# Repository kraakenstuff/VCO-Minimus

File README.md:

# VCO-Minimus
3U Eurorack 3340 based VCO

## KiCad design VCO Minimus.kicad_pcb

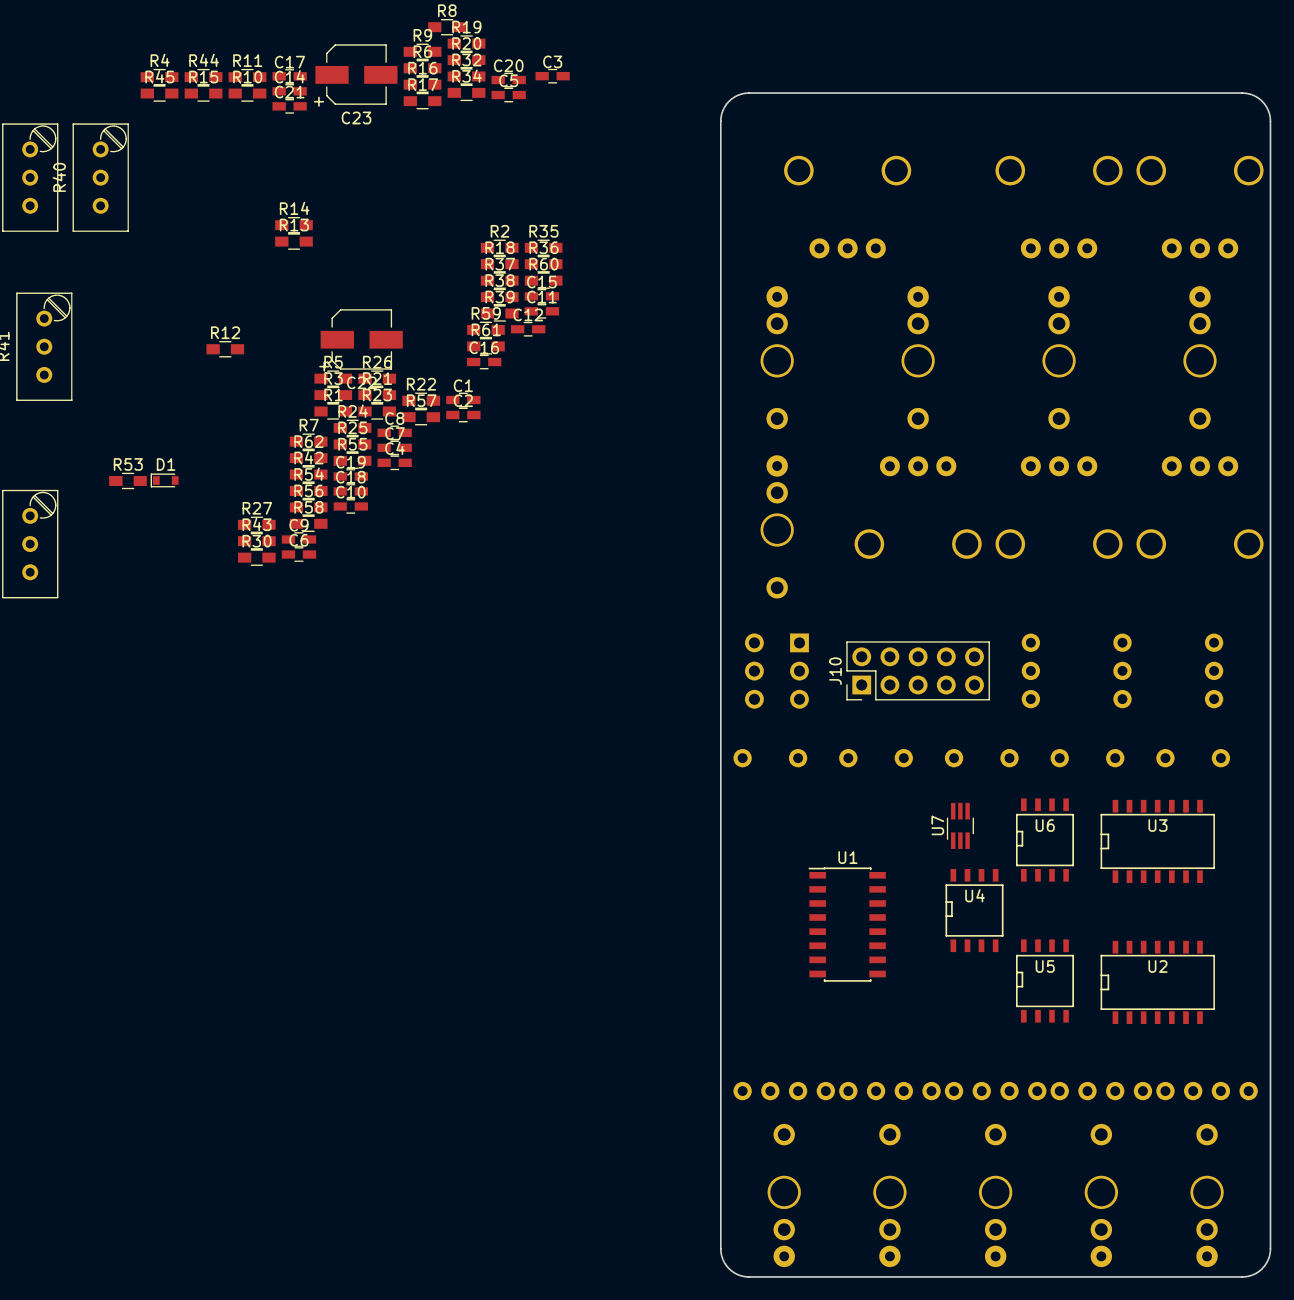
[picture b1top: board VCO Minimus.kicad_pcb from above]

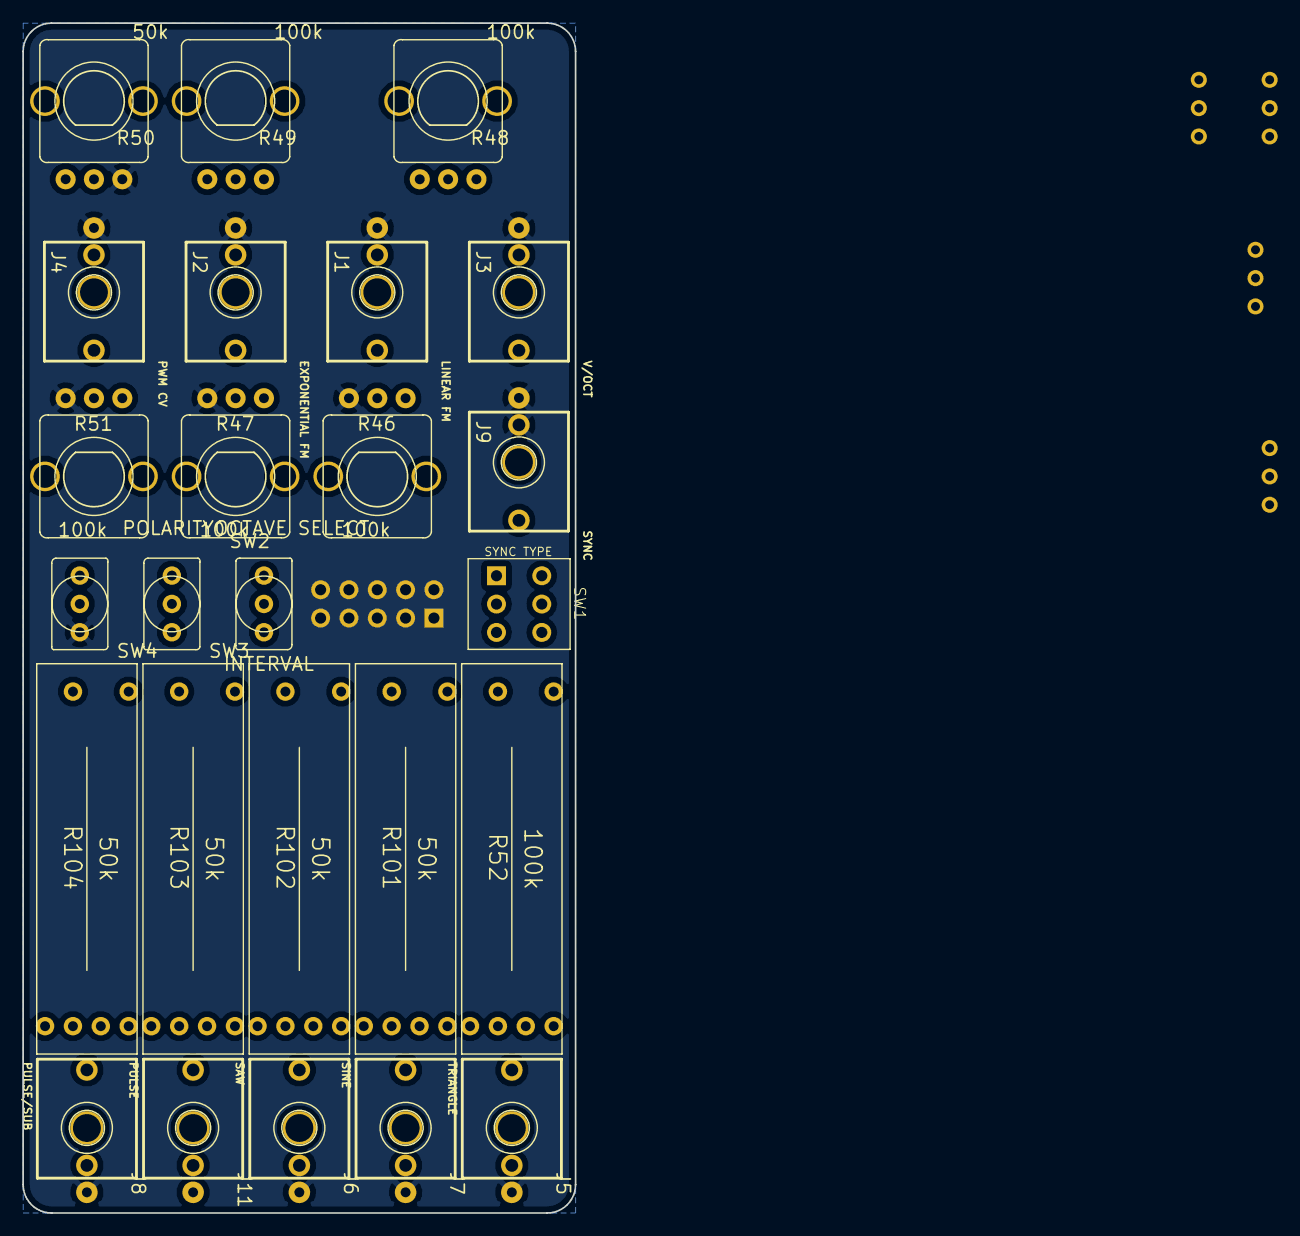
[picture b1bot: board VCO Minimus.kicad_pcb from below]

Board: 2 copper layers, 49.5 x 106.7 mm, 109 parts (25 on the bottom side), 74 nets, no tracks yet.

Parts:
C1: 22p; C_0603_HandSoldering
C2: 33p; C_0603_HandSoldering
C3: 47p; C_0603_HandSoldering
C4, C5, C6: 1n; C_0603_HandSoldering
C7, C8: 10n; C_0603_HandSoldering
C9, C10, C11, C12, C14, C15, C16, C17, C18, C19, C20: 100n; C_0603_HandSoldering
C21: 220n; C_0603_HandSoldering
C22, C23: 10u; CP_Elec_5x5.3
D1: 1N4148; D_0603
J1: LINEAR FM; PJ301M-12
J2: EXPONENTIAL FM; PJ301M-12
J3: V/OCT; PJ301M-12
J4: PWM CV; PJ301M-12
J5: TRIANGLE; PJ301M-12
J6: SAW; PJ301M-12
J7: SINE; PJ301M-12
J8: PULSE/SUB; PJ301M-12
J9: SYNC; PJ301M-12
J10: POWER; Pin_Header_Straight_2x05_Pitch2.54mm
J11: PULSE; PJ301M-12
R1: 390; R_0603_HandSoldering
R2, R3: 470; R_0603_HandSoldering
R4: 820; R_0603_HandSoldering
R5, R6: 1.5k; R_0603_HandSoldering
R7, R8: 1.8k; R_0603_HandSoldering
R9, R10: 2k; R_0603_HandSoldering
R11, R12: 2.2k; R_0603_HandSoldering
R13, R14, R15: 3k; R_0603_HandSoldering
R16, R17: 5.6k; R_0603_HandSoldering
R18, R19, R20, R21, R22, R23, R24, R25, R26, R27: 10k; R_0603_HandSoldering
R28, R29: 10k; Potentiometer_Trimmer_Bourns_3296W
R30: 15k; R_0603_HandSoldering
R32, R34: 20k; R_0603_HandSoldering
R35: 22k; R_0603_HandSoldering
R36: 24k; R_0603_HandSoldering
R37: 30k; R_0603_HandSoldering
R38, R39: 47k; R_0603_HandSoldering
R40, R41: 50k; Potentiometer_Trimmer_Bourns_3296W
R42, R43, R44, R45: 100k; R_0603_HandSoldering
R46, R47, R48, R49, R51: 100k; POT-9MM-ALPHA
R50: 50k; POT-9MM-ALPHA
R52: 100k; POT-SLIDER-LED-ALPHA-RA2045F-20
R53: 120k; R_0603_HandSoldering
R54: 300k; R_0603_HandSoldering
R55: 360k; R_0603_HandSoldering
R56, R57, R58, R59: 1M; R_0603_HandSoldering
R60: 1.5M; R_0603_HandSoldering
R61: 3.3M; R_0603_HandSoldering
R62: 10M; R_0603_HandSoldering
R101, R102, R103, R104: 50k; POT-SLIDER-LED-ALPHA-RA2045F-20
SW1: SYNC TYPE; DPDT_Toggle_108-2MD1T2B3M1QE-EVX
SW2: INTERVAL; SPDT-SUB
SW3: OCTAVE SELECT; SPDT-SUB
SW4: POLARITY; SPDT-SUB
U1: CEM3340; SOIC-16_3.9x9.9mm_Pitch1.27mm
U2: CD4070; SOIC-14_N
U3: CD4013; SOIC-14_N
U4, U5: TL072; SOIC-8-N
U6: TL071; SOIC-8-N
U7: DMMT3904W; SOT-363_SC-70-6_Handsoldering

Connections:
+12V: C11.2, C12.1, C18.1, C19.1, C20.1, C23.1, J10.9, J10.10, R22.2, R23.2, R26.2, R34.1, R37.1, R48.1, R49.1, R50.1, R55.2, R60.1, R62.2, SW4.3, U2.14, U3.14, U4.8, U5.8, U6.7
-12V: C15.2, C16.2, C17.2, C22.2, J10.1, J10.2, R4.1, R41.2, R48.3, R49.3, U4.4, U5.4, U6.4
GND: C2.1, C3.1, C4.2, C6.1, C7.1, C8.1, C9.2, C10.1, C11.1, C12.2, C14.1, C15.1, C16.1, C17.1, C18.2, C19.2, C20.2, C22.1, C23.2, J1.1, J2.1, J3.1, J4.1, J5.1, J6.1, J7.1, J8.1, J9.1, J9.2, J10.3, J10.4, J10.5, J10.6, J10.7, J10.8, R7.2, R8.2, R10.2, R11.1, R12.1, R13.1, R14.2, R19.1, R20.1, R21.1, R29.1, R46.3, R47.3, R50.3, R51.3, SW4.1, U1.12, U2.2, U2.7, U2.9, U3.4, U3.6, U3.7, U3.8, U3.10, U6.3
unnamed: C1.1, R26.1, R27.1, U5.6
unnamed: C1.2, R15.1, R27.2, U5.7
unnamed: C2.2, R24.2, U5.3
unnamed: C3.2, R35.2, R59.1, U2.1
unnamed: C4.1, U1.11
unnamed: C5.1, J9.3
unnamed: C5.2, SW1.5
unnamed: C6.2, R18.2, R58.1, U1.5
unnamed: C7.2, R3.1
unnamed: C8.2, R2.1
unnamed: C9.1, U1.16
unnamed: C10.2, R4.2, R16.1, R28.2, U1.3
unnamed: C14.2, SW1.3
unnamed: C21.1, R46.1
unnamed: C21.2, J1.3
unnamed: D1.1, R17.1, R20.2
unnamed: D1.2, U1.6
unnamed: J2.3, R47.1
unnamed: J3.3, R43.2
unnamed: J4.3, R51.1
unnamed: J5.3, R5.2, R13.2
unnamed: J6.3, R6.2, R14.1
unnamed: J7.3, R9.2, R10.1
unnamed: J8.3, R8.1, R15.2
unnamed: R1.1, R41.1, U7.4
unnamed: R1.2, R41.3, U7.5
unnamed: R2.2, R42.1, R43.1, R44.2, R55.1, R57.2, R61.2, U1.15
unnamed: R3.2, R56.1, R60.2, U1.13
unnamed: R7.1, U1.14
unnamed: R11.2, R40.1, U7.1
unnamed: R12.2, U7.2
unnamed: R16.2, U1.2
unnamed: R17.2, SW1.6
unnamed: R18.1, R53.2, U6.6
unnamed: R21.2, R30.1, R37.2, U4.6
unnamed: R22.1, U4.2, U7.6
unnamed: R23.1, R32.1, U4.3, U7.3
unnamed: R25.1, R34.2, U5.2
unnamed: R6.1, R25.2, U5.1
unnamed: R28.1, R36.1
unnamed: R29.2, R57.1
unnamed: R29.3, U1.7
unnamed: R5.1, R30.2, R39.1, U4.7
unnamed: R9.1, R32.2, U4.1
unnamed: R36.2, U1.1
unnamed: R38.1, SW1.2
unnamed: R38.2, U1.9
unnamed: R39.2, R40.2, R40.3
unnamed: R42.2, R47.2
unnamed: R44.1, R48.2
unnamed: R45.1, R51.2
unnamed: R45.2, R53.1, R54.2, R62.1, U6.2
unnamed: R46.2, R56.2
unnamed: R49.2, R61.1
unnamed: R50.2, R54.1
unnamed: R52.P1, U2.10
unnamed: R52.P2, U5.5
unnamed: R52.P3, SW3.2
unnamed: R59.2, SW2.1, U2.3, U2.5, U2.8
unnamed: SW1.1, SW1.4
unnamed: SW2.2, U2.12
unnamed: SW2.3, U2.4
unnamed: SW3.1, U3.1
unnamed: SW3.3, U3.13
unnamed: SW4.2, U2.13
unnamed: U2.6, U3.9, U3.12
unnamed: U2.11, U3.3
unnamed: U3.2, U3.5, U3.11
PULSE: R19.2, R35.1, R58.2, U1.4
SAW: R24.1, U1.8
TRI: U1.10, U4.5
